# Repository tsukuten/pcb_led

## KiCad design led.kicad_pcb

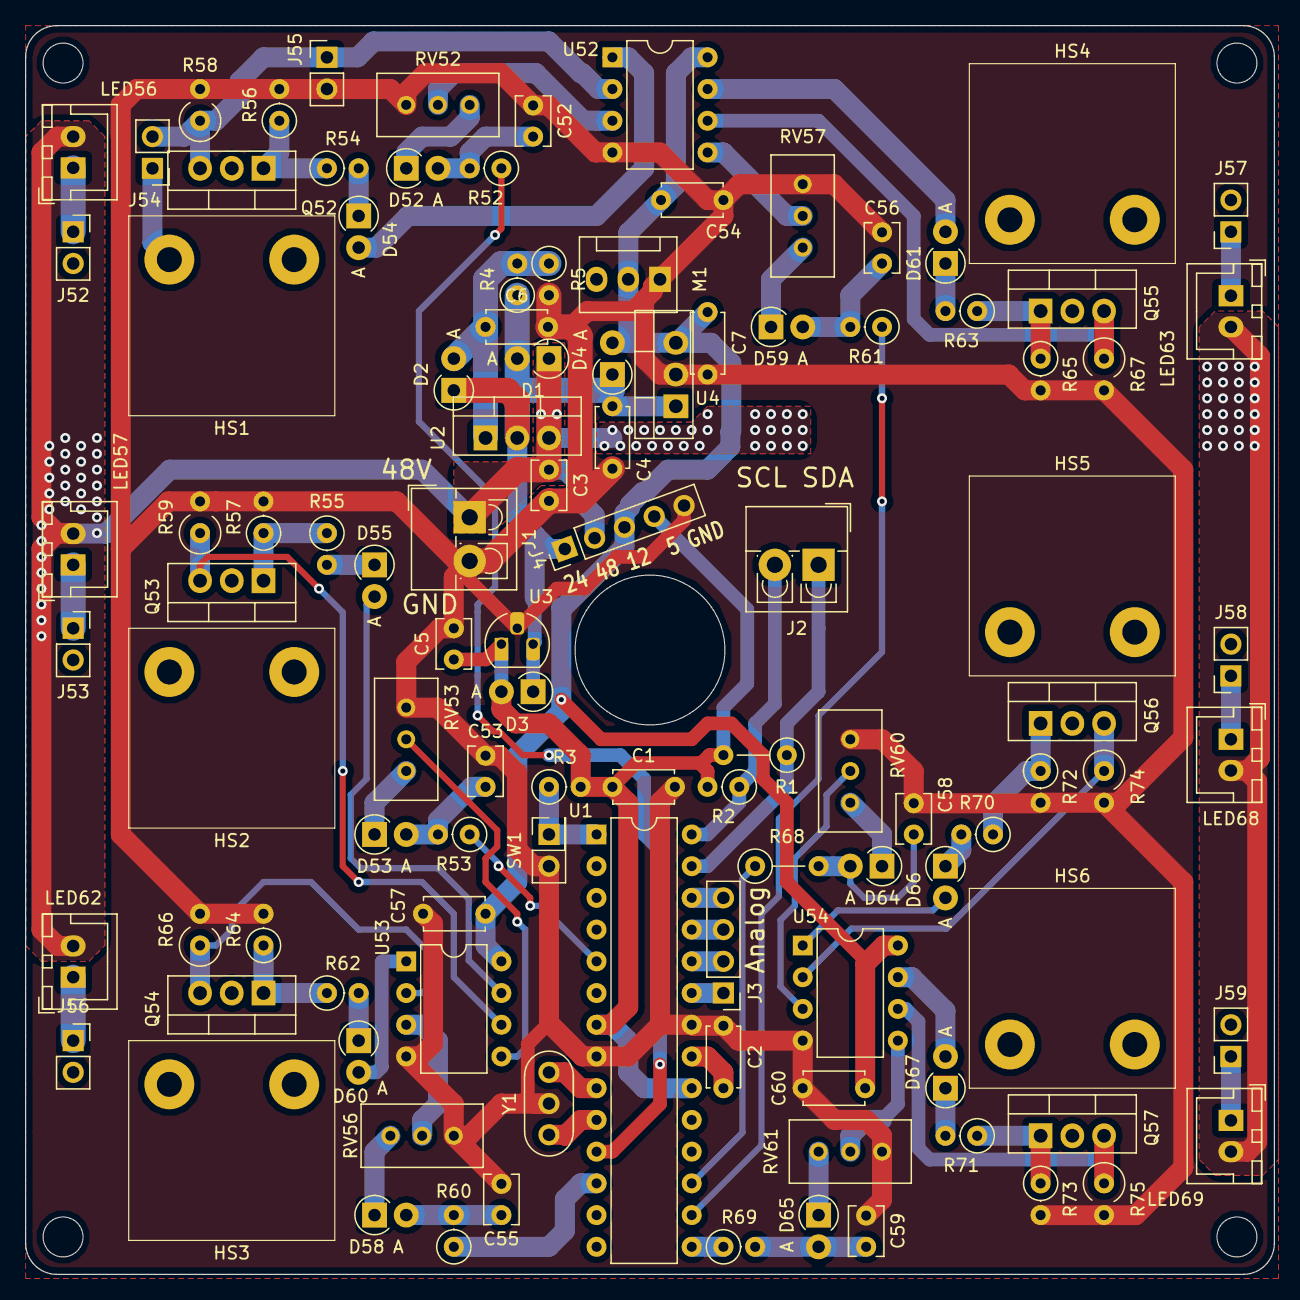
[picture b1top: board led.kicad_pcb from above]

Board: 2 copper layers, 100.0 x 100.0 mm, 107 parts (0 on the bottom side), 76 nets.

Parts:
C1, C2, C4, C6, C7, C54, C57, C60: 10u; C_Disc_D4.7mm_W2.5mm_P5.00mm
C3, C5, C52, C53, C55, C56, C58, C59: 1u; C_Disc_D3.8mm_W2.6mm_P2.50mm
D1, D2, D3, D4: 1SS178; D_T-1_P2.54mm_Vertical_AnodeUp
D52, D53, D54, D55, D58, D59, D60, D61, D64, D65, D66, D67: 1V0; D_T-1_P2.54mm_Vertical_AnodeUp
HS1: Heatsink_FET_1; 16PB017-01025
HS2: Heatsink_FET_2; 16PB017-01025
HS3: Heatsink_FET_3; 16PB017-01025
HS4: Heatsink_FET_4; 16PB017-01025
HS5: Heatsink_FET_5; 16PB017-01025
HS6: Heatsink_FET_6; 16PB017-01025
J1: Slip_ring_48V; TerminalBlock_4Ucon_1x02_P3.50mm_Vertical
J2: Slip_ring_I2C; TerminalBlock_4Ucon_1x02_P3.50mm_Vertical
J3: Analog_input; PinHeader_1x04_P2.54mm_Vertical
J4: Test_power; PinHeader_1x05_P2.54mm_Vertical
J52: Jump_ID_1; PinSocket_1x02_P2.54mm_Vertical
J53: Jump_ID_2; PinSocket_1x02_P2.54mm_Vertical
J54: Test_Vds; PinHeader_1x02_P2.54mm_Vertical
J55: Test_sense; PinHeader_1x02_P2.54mm_Vertical
J56: Jump_ID_3; PinSocket_1x02_P2.54mm_Vertical
J57: Jump_ID_4; PinSocket_1x02_P2.54mm_Vertical
J58: Jump_ID_5; PinSocket_1x02_P2.54mm_Vertical
J59: Jump_ID_6; PinSocket_1x02_P2.54mm_Vertical
LED56, LED57, LED62, LED63, LED68, LED69: LED; JST_XH_B02B-XH-A_1x02_P2.50mm_Vertical
M1: Fan; FanPinHeader_1x03_P2.54mm_Vertical
Q52, Q53, Q54, Q55, Q56, Q57: EKI04027; TO-220-3_Vertical
R1, R68: 10k; R_Axial_DIN0207_L6.3mm_D2.5mm_P5.08mm_Vertical
R2, R3, R52, R53, R60, R61, R69: 10k; R_Axial_DIN0207_L6.3mm_D2.5mm_P2.54mm_Vertical
R4: 200; R_Axial_DIN0207_L6.3mm_D2.5mm_P2.54mm_Vertical
R5: 3k3; R_Axial_DIN0207_L6.3mm_D2.5mm_P2.54mm_Vertical
R54, R55, R62, R63, R70, R71: 150; R_Axial_DIN0207_L6.3mm_D2.5mm_P2.54mm_Vertical
R56, R57, R64, R65, R72, R73: 47k; R_Axial_DIN0207_L6.3mm_D2.5mm_P2.54mm_Vertical
R58, R59, R66, R67, R74, R75: 1R0; R_Axial_DIN0309_L9.0mm_D3.2mm_P2.54mm_Vertical
RV52, RV53, RV56, RV57, RV60, RV61: 10k; Potentiometer_Bourns_3296W_Vertical
SW1: Reset; PinSocket_2x01_P2.54mm_Vertical
U1: ATmega328P-PU; DIP-28_W7.62mm
U2: LM317_TO220; TO-220-3_Vertical
U3: LM78L05_TO92; TO-92L_HandSolder
U4: LM7812_TO220; TO-220-3_Vertical
U52, U53, U54: NJM13404; DIP-8_W7.62mm
Y1: 8MHz; Resonator-3Pin_W8.0mm_H3.5mm

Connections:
+5V: C1.1, C5.1, D3.2, J4.4, R1.2, R2.2, R3.2, U1.7, U1.20, U3.1
+12V: C7.1, C54.1, C57.1, C60.1, D4.2, J4.3, M1.2, U4.3, U52.8, U53.8, U54.8
+24V: C4.1, D1.2, D2.1, D3.1, D4.1, J4.1, R4.1, U2.2, U3.3, U4.1
+48V: C3.1, D1.1, J1.1, J4.2, LED56.2, LED57.2, LED62.2, LED63.2, LED68.2, LED69.2, U2.3
/ADC0: J3.1, U1.23
/ADC1: J3.2, U1.24
/ADC2: J3.3, U1.25
/ADC3: J3.4, U1.26
/PWM1: R69.1, U1.15
/PWM2: R61.1, U1.16
/PWM3: R68.1, U1.17
/PWM4: R53.1, U1.5
/PWM5: R52.1, U1.11
/PWM6: R60.1, U1.12
/SCL: J2.2, R2.1, U1.28
/SDA: J2.1, R1.1, U1.27
GND: C1.2, C2.2, C3.2, C4.2, C5.2, C6.2, C7.2, C52.2, C53.2, C54.2, C55.2, C56.2, C57.2, C58.2, C59.2, C60.2, J1.2, J4.5, J55.2, M1.1, R5.2, R56.2, R57.2, R58.2, R59.2, R64.2, R65.2, R66.2, R67.2, R72.2, R73.2, R74.2, R75.2, RV52.3, RV53.3, RV56.3, RV57.3, RV60.3, RV61.3, SW1.2, U1.8, U1.22, U3.2, U4.2, U52.4, U53.4, U54.4, Y1.2
unnamed: C2.1, U1.21
unnamed: C6.1, D2.2, R4.2, R5.1, U2.1
unnamed: C52.1, D52.2, R52.2
unnamed: C53.1, D53.2, R53.2
unnamed: C55.1, D58.2, R60.2
unnamed: C56.1, D59.2, R61.2
unnamed: C58.1, D64.2, R68.2
unnamed: C59.1, D65.2, R69.2
unnamed: D52.1, RV52.1
unnamed: D53.1, RV53.1
unnamed: D54.1, R54.2
unnamed: D54.2, U52.1
unnamed: D55.1, R55.2
unnamed: D55.2, U53.7
unnamed: D58.1, RV56.1
unnamed: D59.1, RV57.1
unnamed: D60.1, R62.2
unnamed: D60.2, U53.1
unnamed: D61.1, R63.2
unnamed: D61.2, U52.7
unnamed: D64.1, RV60.1
unnamed: D65.1, RV61.1
unnamed: D66.1, R70.2
unnamed: D66.2, U54.1
unnamed: D67.1, R71.2
unnamed: D67.2, U54.7
unnamed: HS1.1, J52.2, J54.1, Q52.2
unnamed: HS2.1, J53.2, Q53.2
unnamed: HS3.1, J56.2, Q54.2
unnamed: HS4.1, J57.2, Q55.2
unnamed: HS5.1, J58.2, Q56.2
unnamed: HS6.1, J59.2, Q57.2
unnamed: J52.1, LED56.1
unnamed: J53.1, LED57.1
unnamed: J54.2, J55.1, Q52.3, R58.1, U52.2
unnamed: J56.1, LED62.1
unnamed: J57.1, LED63.1
unnamed: J58.1, LED68.1
unnamed: J59.1, LED69.1
unnamed: Q52.1, R54.1, R56.1
unnamed: Q53.1, R55.1, R57.1
unnamed: Q53.3, R59.1, U53.6
unnamed: Q54.1, R62.1, R64.1
unnamed: Q54.3, R66.1, U53.2
unnamed: Q55.1, R63.1, R65.1
unnamed: Q55.3, R67.1, U52.6
unnamed: Q56.1, R70.1, R72.1
unnamed: Q56.3, R74.1, U54.2
unnamed: Q57.1, R71.1, R73.1
unnamed: Q57.3, R75.1, U54.6
unnamed: R3.1, SW1.1, U1.1
unnamed: RV52.2, U52.3
unnamed: RV53.2, U53.5
unnamed: RV56.2, U53.3
unnamed: RV57.2, U52.5
unnamed: RV60.2, U54.3
unnamed: RV61.2, U54.5
unnamed: U1.9, Y1.1
unnamed: U1.10, Y1.3

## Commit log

2018-09-26 Add .gitignore
2018-09-26 Add semi-completed schematic files
2018-09-26 schematic: Use vertical footprints for axial components
2018-09-26 Add an WIP PCB files
2018-09-27 schematic: Change order of opamps
2018-09-27 schematic: Remove redundant fans
    The PCB is too small to place many fans, so leaved only one.
2018-09-27 schematic: Change the order of PWM pins
2018-09-29 schematic: Remove POTs on negative feedback
    Sense voltage (~0.6V) is small enough without POT.
2018-09-29 schematic: Replace NJM4580 with NJM13404 which supports unity gain
2018-09-29 schematic: Replace FKI10531 with EKI04027 because of heat dispassion
2018-09-29 schematic: Use more precise POT
2018-09-29 schematic: Change footprints and pin assignments for PCB
2018-09-30 schematic: Add external connector for analog inputs and power testing
2018-09-30 PCB: Complete wiring
2018-09-30 PCB: Add fill zones of power
2018-09-30 PCB: Move silks not to conflict with coppers
2018-09-30 PCB: Add more silks
2018-09-30 Bump to v0.0.0

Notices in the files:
led.kicad_pcb:
(c) 2018 Tsukuba Univ. Astronomy Club
